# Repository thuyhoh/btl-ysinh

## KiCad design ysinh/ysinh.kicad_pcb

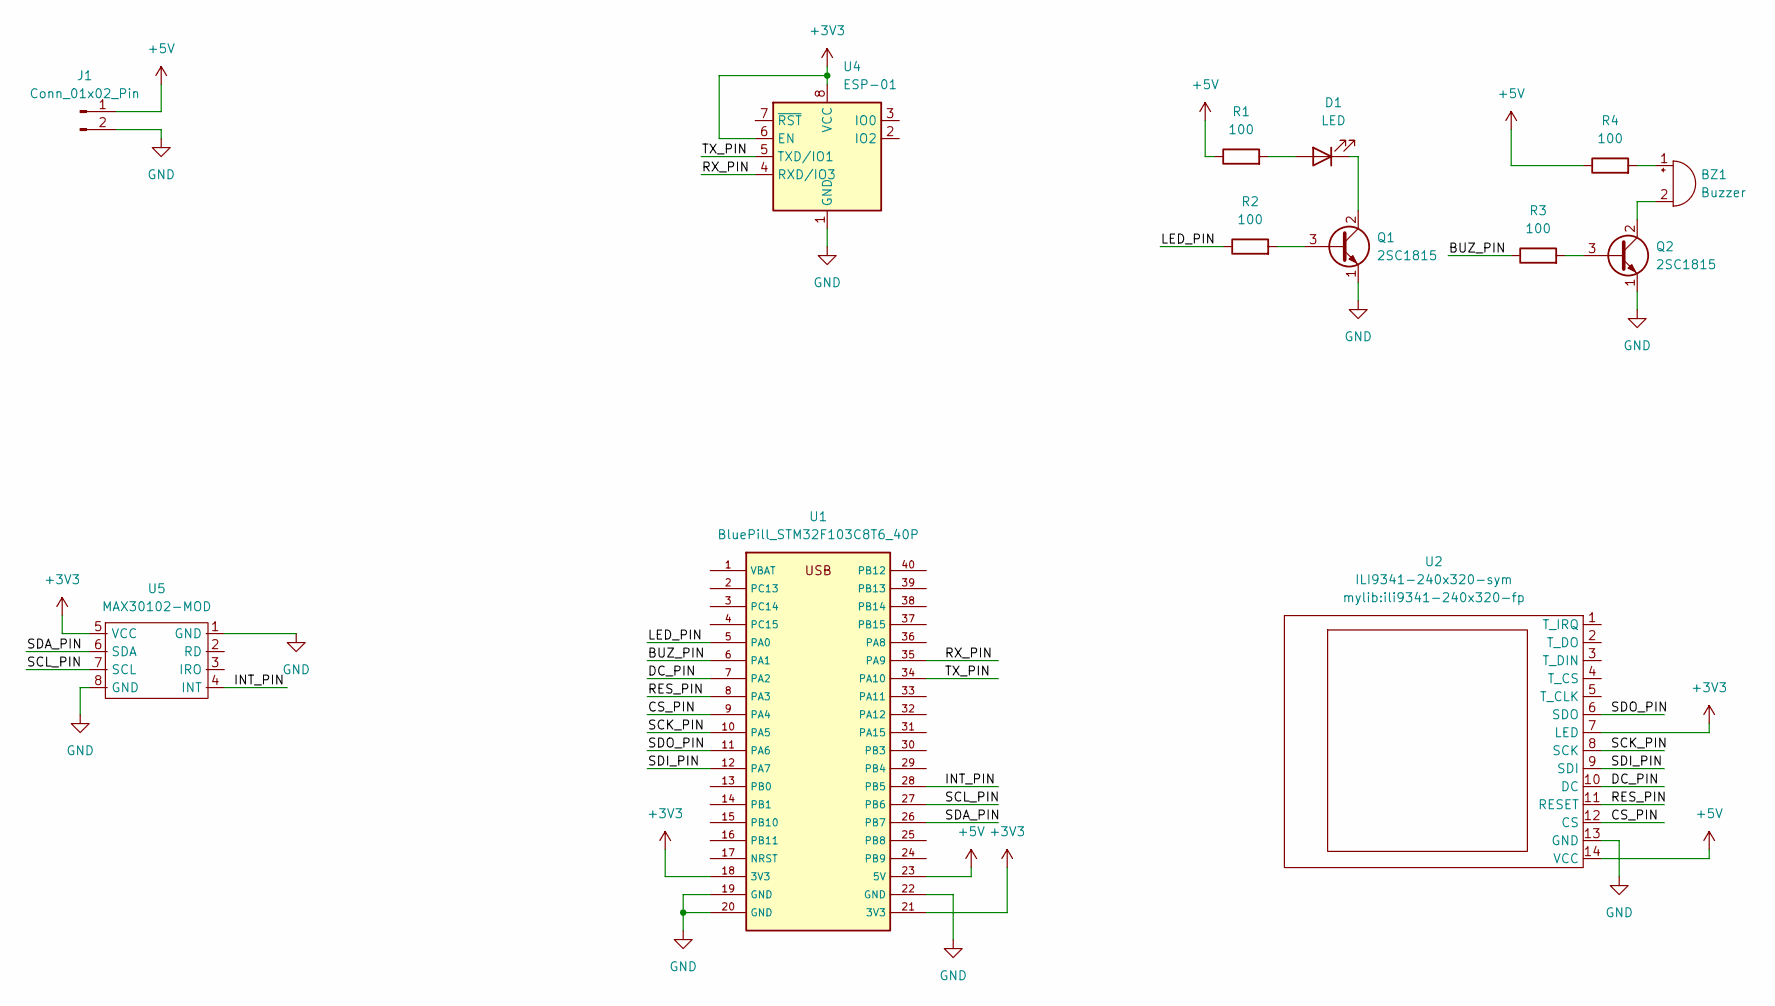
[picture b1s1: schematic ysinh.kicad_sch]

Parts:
BZ1: Buzzer; Buzzer_12x9.5RM7.6
D1: LED; LED_D3.0mm_Horizontal_O1.27mm_Z10.0mm
J1: Conn_01x02_Pin; PinHeader_1x02_P2.54mm_Vertical
Q1, Q2: 2SC1815; TO-92_Inline
R1, R2, R3, R4: 100; R_Axial_DIN0207_L6.3mm_D2.5mm_P10.16mm_Horizontal
U1: BluePill_STM32F103C8T6_40P; BluePill_40P_P2.54mm_W15.24mm
U2: ILI9341-240x320-sym; ili9341-240x320-fp
U4: ESP-01
U5: MAX30102-MOD; max30102-mod-fp

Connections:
+3V3: U1.18 (3V3), U1.21 (3V3), U2.7 (LED), U4.6 (EN), U4.8 (VCC), U5.5 (VCC); also elsewhere on the board
+5V: J1.1, R1.1, R4.1, U1.23 (5V), U2.14 (VCC); also elsewhere on the board
/BUZ_PIN: R3.1, U1.6 (PA1)
/CS_PIN: U1.9 (PA4), U2.12 (CS); also elsewhere on the board
/DC_PIN: U1.7 (PA2), U2.10 (DC); also elsewhere on the board
/INT_PIN: U1.28 (PB5), U5.4 (INT)
/LED_PIN: R2.1, U1.5 (PA0)
/RES_PIN: U1.8 (PA3), U2.11 (RESET); also elsewhere on the board
/RX_PIN: U1.35 (PA9), U4.4 (RXD/IO3)
/SCK_PIN: U1.10 (PA5), U2.8 (SCK); also elsewhere on the board
/SCL_PIN: U1.27 (PB6), U5.7 (SCL)
/SDA_PIN: U1.26 (PB7), U5.6 (SDA)
/SDI_PIN: U1.12 (PA7), U2.9 (SDI); also elsewhere on the board
/SDO_PIN: U1.11 (PA6), U2.6 (SDO); also elsewhere on the board
/TX_PIN: U1.34 (PA10), U4.5 (TXD/IO1)
GND: J1.2, Q1.1 (E), Q2.1 (E), U1.19 (GND), U1.20 (GND), U1.22 (GND), U2.13 (GND), U4.1 (GND), U5.1 (GND), U5.8 (GND); also elsewhere on the board
unnamed: BZ1.1 (+), R4.2
unnamed: BZ1.2 (-), Q2.2 (C)
unnamed: D1.2 (A), R1.2
unnamed: D1.1 (K), Q1.2 (C)
unnamed: Q1.3 (B), R2.2
unnamed: Q2.3 (B), R3.2

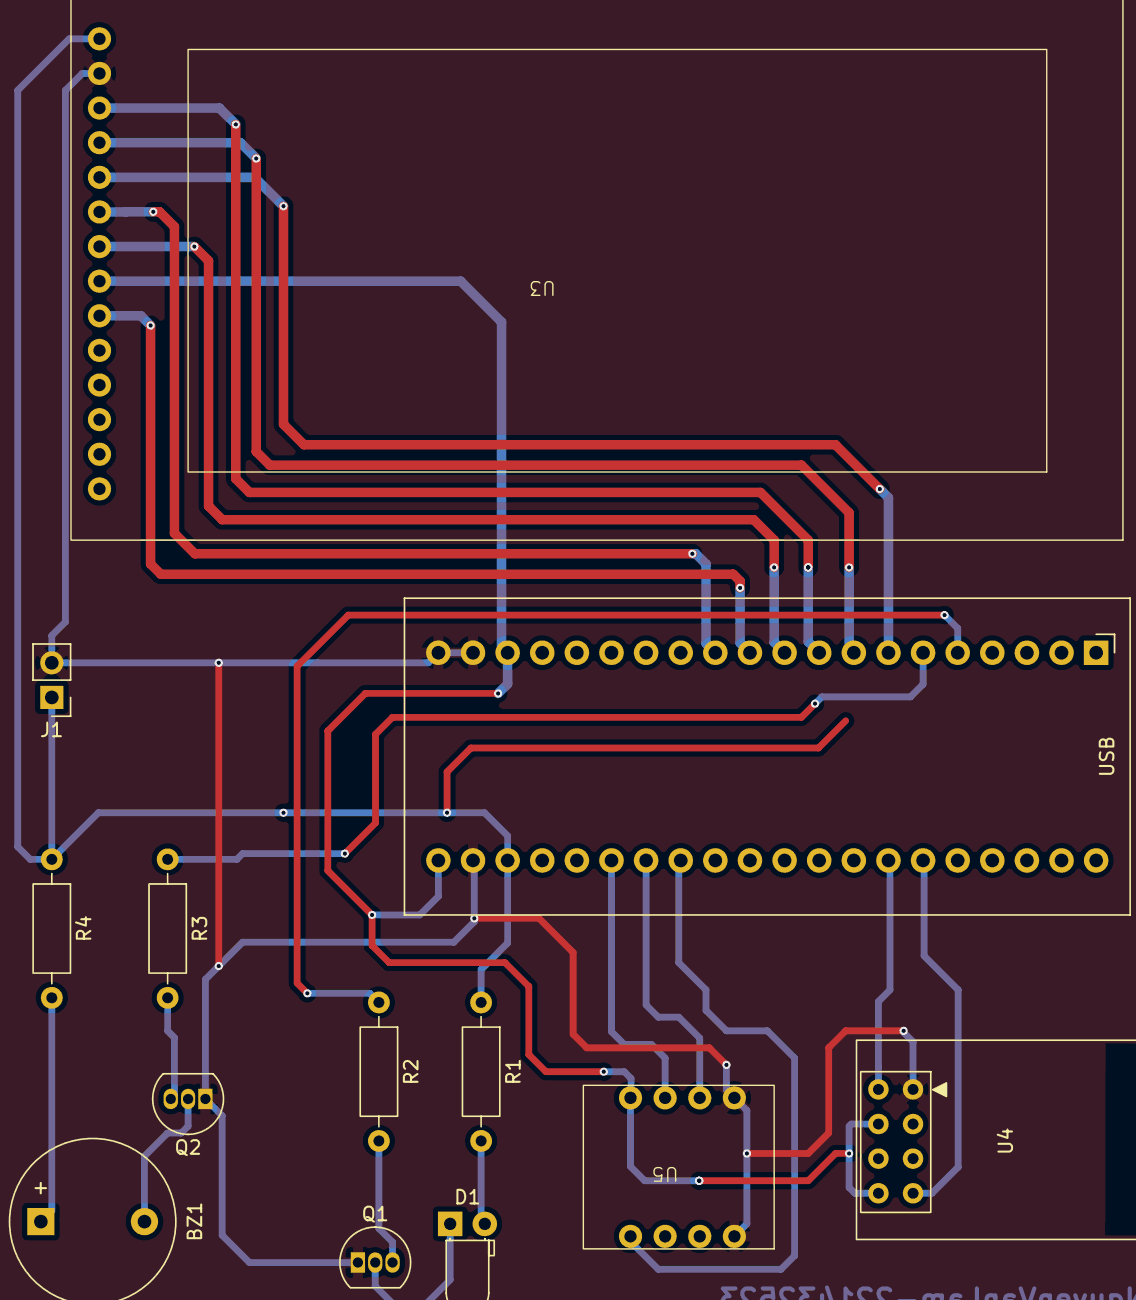
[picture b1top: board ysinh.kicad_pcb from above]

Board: 2 copper layers, 13 parts (0 on the bottom side), 22 nets.

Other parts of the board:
U3: ILI9341-240x320-sym; ili9341-240x320-fp

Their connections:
+3V3: U3.7 (LED); also elsewhere on the board
+5V: U3.14 (VCC); also elsewhere on the board
/CS_PIN: U3.12 (CS); also elsewhere on the board
/DC_PIN: U3.10 (DC); also elsewhere on the board
/RES_PIN: U3.11 (RESET); also elsewhere on the board
/SCK_PIN: U3.8 (SCK); also elsewhere on the board
/SDI_PIN: U3.9 (SDI); also elsewhere on the board
/SDO_PIN: U3.6 (SDO); also elsewhere on the board
GND: U3.13 (GND); also elsewhere on the board
